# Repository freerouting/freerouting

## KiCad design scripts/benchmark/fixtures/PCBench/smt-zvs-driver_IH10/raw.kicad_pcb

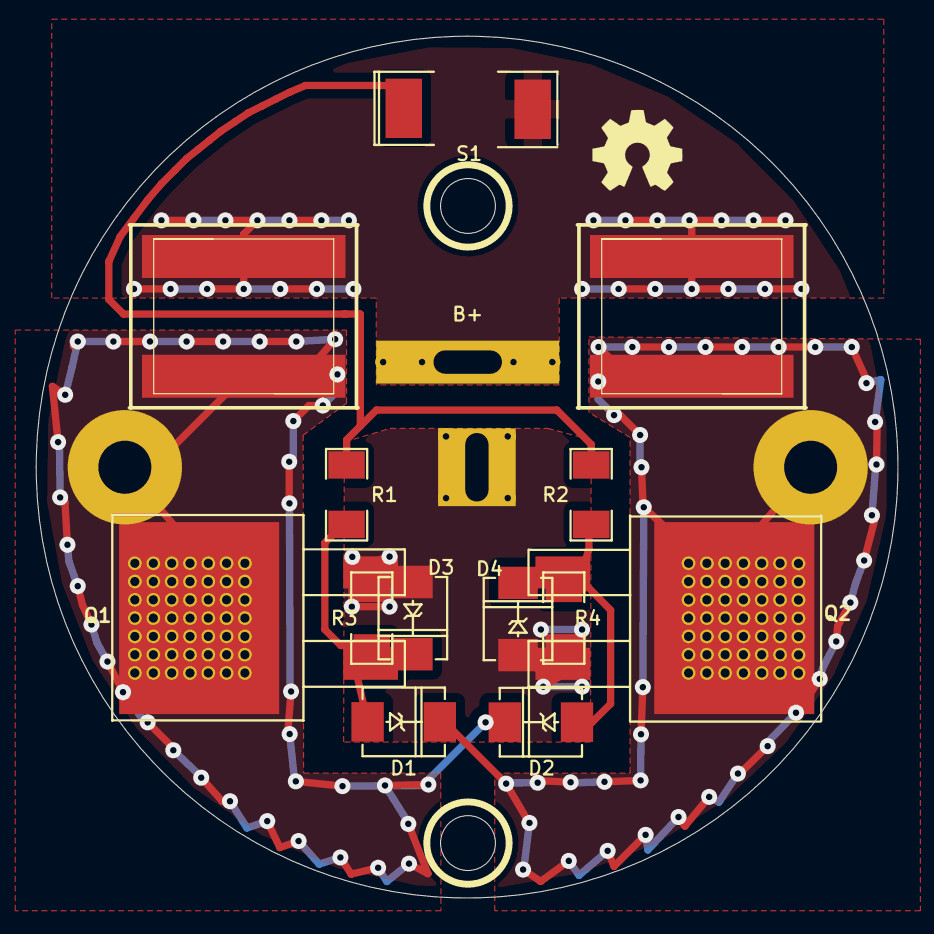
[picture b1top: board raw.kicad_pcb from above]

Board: 2 copper layers, 47.9 x 47.9 mm, 17 parts (0 on the bottom side), 7 nets.

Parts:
B+: DeanConn
D1, D2: DIODE; DO214
D3, D4: ZENER; DO214
L1, L2: INDUCTOR; inductor-coilcraft-xal1010-102
Q1: MOSFET_N; DPAKGDS-TVSM-Q1
Q2: MOSFET_N; DPAKGDS-TVSM-Q2
R1, R2: 270; SM1206
R3, R4: 10K; SM1206
S1: Val**; SM2112L
endcap: VAL**; endcap
mount: P***; 1pin
mount#2: P***; 1pin

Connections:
+BATT: B+.1, L1.1, L2.1, S1.2
GND: B+.2, D3.1, D4.1, Q1.S, Q2.S, R3.2, R4.2
unnamed: D2.1, D4.2, Q2.G, R2.2, R4.1
unnamed: D1.1, D3.2, Q1.G, R1.2, R3.1
unnamed: R1.1, R2.1, S1.1
unnamed: D2.2, L1.2, Q1.D
unnamed: D1.2, L2.2, Q2.D

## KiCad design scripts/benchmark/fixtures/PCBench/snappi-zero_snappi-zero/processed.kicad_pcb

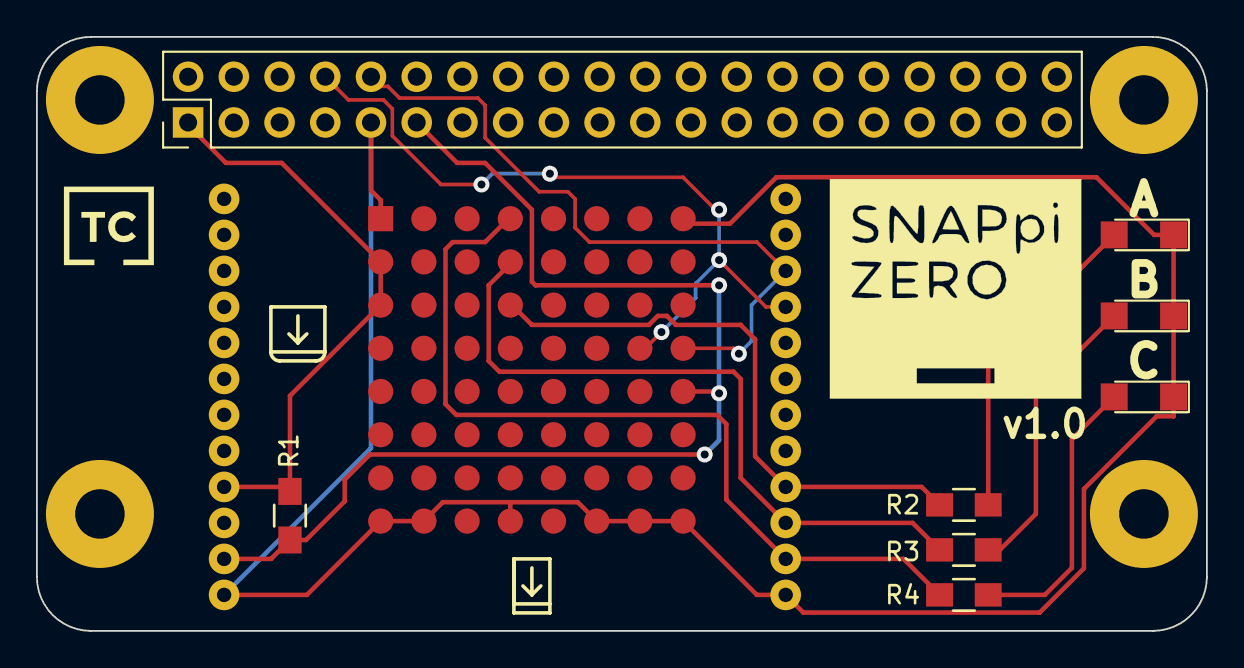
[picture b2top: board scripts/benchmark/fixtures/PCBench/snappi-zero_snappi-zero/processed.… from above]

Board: 2 copper layers, 65.0 x 33.0 mm, 11 parts (0 on the bottom side), 11 nets.

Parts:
D1: A; LED_1206
D2: B; LED_1206
D3: C; LED_1206
P1: CONN_02X20; Raspberry_Pi_Zero
R1: 10k; R_0805_HandSoldering
R2, R3, R4: 1k; R_0805_HandSoldering
U1: RF200; RF200_nosilk
U2: SM220UF1; SM200_nosilk
svg2mod: G***; tc_30mm

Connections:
3v3: P1.1, R1.1, U1.21, U2.A2, U2.A3
GND: D1.1, D2.1, D3.1, P1.9, U1.1, U1.24, U2.A1, U2.A8, U2.B8, U2.D8, U2.F8, U2.G8, U2.H1, U2.H8
GPIO_17: P1.11, R1.2, U1.23, U2.H5
LED_A: R2.1, U1.4, U2.D3
LED_B: R3.2, U1.3, U2.D2
LED_C: R4.2, U1.2, U2.D1
unnamed: D1.2, R2.2
unnamed: D2.2, R3.1
unnamed: D3.2, R4.1
PI_RX: P1.10, U1.10, U2.H4
PI_TX: P1.8, U1.9, U2.G4

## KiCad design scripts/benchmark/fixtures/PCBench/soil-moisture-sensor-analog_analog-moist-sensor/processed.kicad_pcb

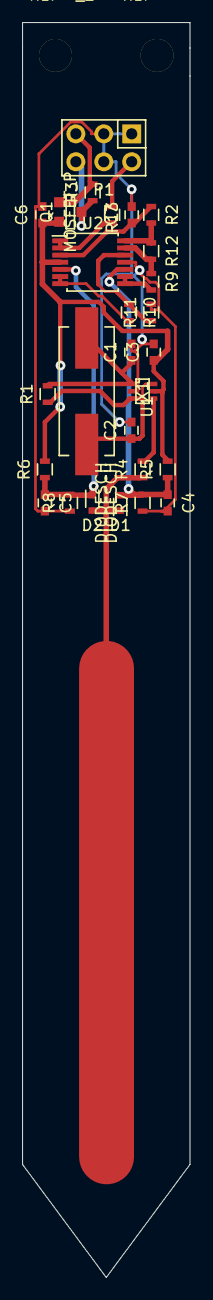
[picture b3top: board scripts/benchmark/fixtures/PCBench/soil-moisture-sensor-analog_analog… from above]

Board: 2 copper layers, 15.2 x 114.2 mm, 27 parts (0 on the bottom side), 18 nets.

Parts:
C1, C2: 18p; C_0603
C3, C6, C7: 1u; C_0603
C4, C5: 1n; C_0603
D1, D2: DIODESCH; SOD-523
P1: CONN_01X06; Pin_Header_Straight_2x03
Q1: MOSFET_P; SOT-23-GDS
R1, R3, R5, R6, R7, R8: 1M; R_0603
R2: 10k; R_0603
R4, R13: 330; R_0603
R9, R10, R11, R12: 10k 0.1%; R_0603
U1: NC7WZU04P6; sc70-6
U2: LM324; TSSOP-14_4.4x5mm_Pitch0.65mm
X1: 16MHz; Crystal_HC49-SD_SMD

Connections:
/OUT: P1.2, R13.1
/SENSE_HIGH: C5.1, D2.2, R6.1, R8.2, U2.5
/SENSE_LOW: C4.1, D1.1, R5.1, R7.2, U2.10
/SENSOR_TRACK: D1.2, D2.1, R4.1
/~ENABLE: P1.5, Q1.G, R3.2
GND: C1.2, C2.2, C3.2, C4.2, C5.2, C6.2, C7.2, P1.1, P1.3, P1.4, R7.1, R8.1, R11.2, U1.2, U2.11
unnamed: C1.1, R1.2, U1.1, X1.1
unnamed: C2.1, R1.1, U1.3, U1.6, X1.2
unnamed: C7.1, R2.1, U2.3
unnamed: R4.2, U1.4
unnamed: R9.2, U2.8, U2.9
unnamed: R10.1, R11.1, U2.12
unnamed: R10.2, U2.6, U2.7
unnamed: R2.2, R12.1, U2.14
unnamed: R9.1, R12.2, U2.13
unnamed: R13.2, U2.1, U2.2
VCC: C3.1, C6.1, Q1.S, R5.2, R6.2, U1.5, U2.4
VDD: P1.6, Q1.D, R3.1

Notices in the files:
scripts/benchmark/fixtures/PCBench/snappi-zero_snappi-zero/processed.kicad_pcb:
CC-BY-SA 4.0
